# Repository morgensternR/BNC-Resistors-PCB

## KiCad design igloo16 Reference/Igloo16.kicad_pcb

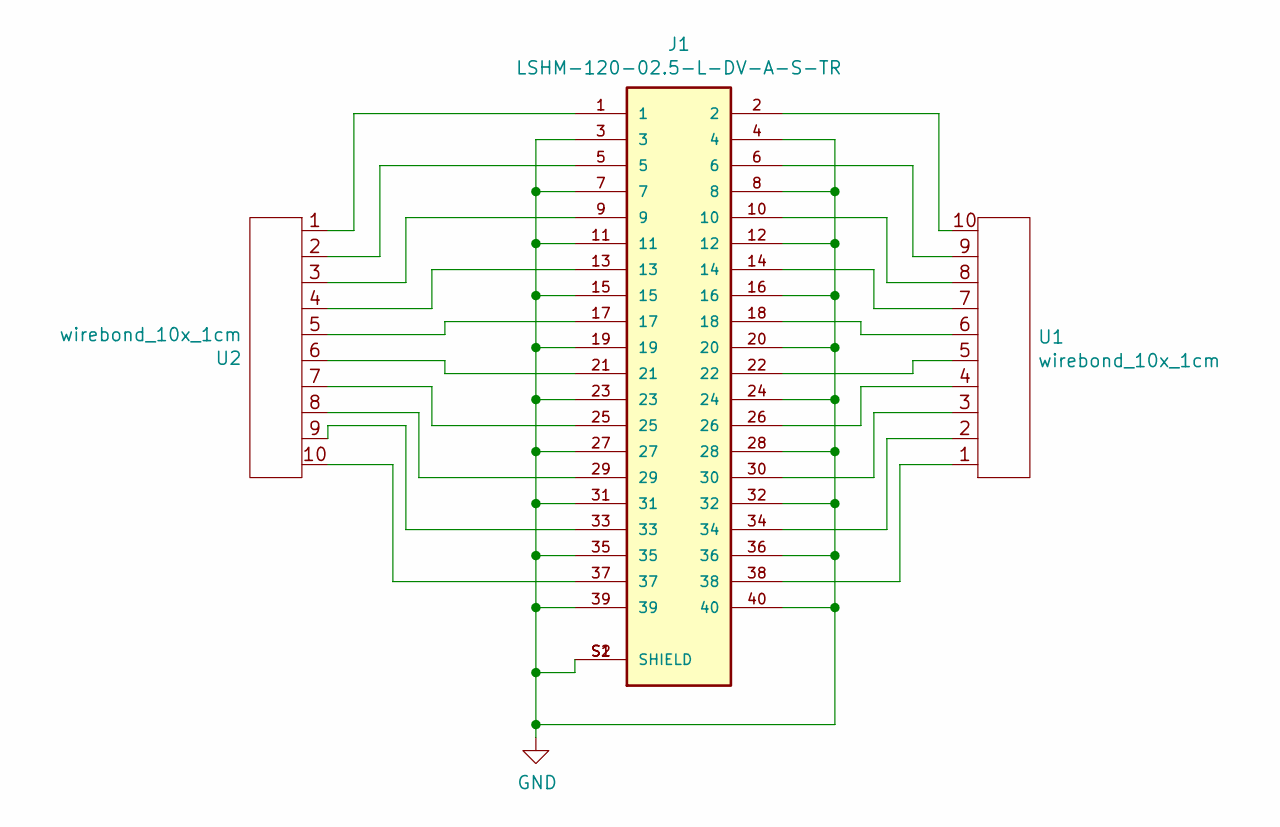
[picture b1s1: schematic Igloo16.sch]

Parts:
J1: LSHM-120-02.5-L-DV-A-S-TR; SAMTEC_LSHM-120-02.5-L-DV-A-S-TR
U1, U2: wirebond_10x_1cm

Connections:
GND: J1.3, J1.4, J1.7, J1.8, J1.11, J1.12, J1.15, J1.16, J1.19, J1.20, J1.23, J1.24, J1.27, J1.28, J1.31, J1.32, J1.35, J1.36, J1.39, J1.40, J1.S1 (SHIELD), J1.S2 (SHIELD)
unnamed: J1.1, U2.1
unnamed: J1.2, U1.10
unnamed: J1.5, U2.2
unnamed: J1.6, U1.9
unnamed: J1.9, U2.3
unnamed: J1.10, U1.8
unnamed: J1.13, U2.4
unnamed: J1.14, U1.7
unnamed: J1.17, U2.5
unnamed: J1.18, U1.6
unnamed: J1.21, U2.6
unnamed: J1.22, U1.5
unnamed: J1.25, U2.7
unnamed: J1.26, U1.4
unnamed: J1.29, U2.8
unnamed: J1.30, U1.3
unnamed: J1.33, U2.9
unnamed: J1.34, U1.2
unnamed: J1.37, U2.10
unnamed: J1.38, U1.1

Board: 2 copper layers, 3 parts (1 on the bottom side), 21 nets, no tracks yet.

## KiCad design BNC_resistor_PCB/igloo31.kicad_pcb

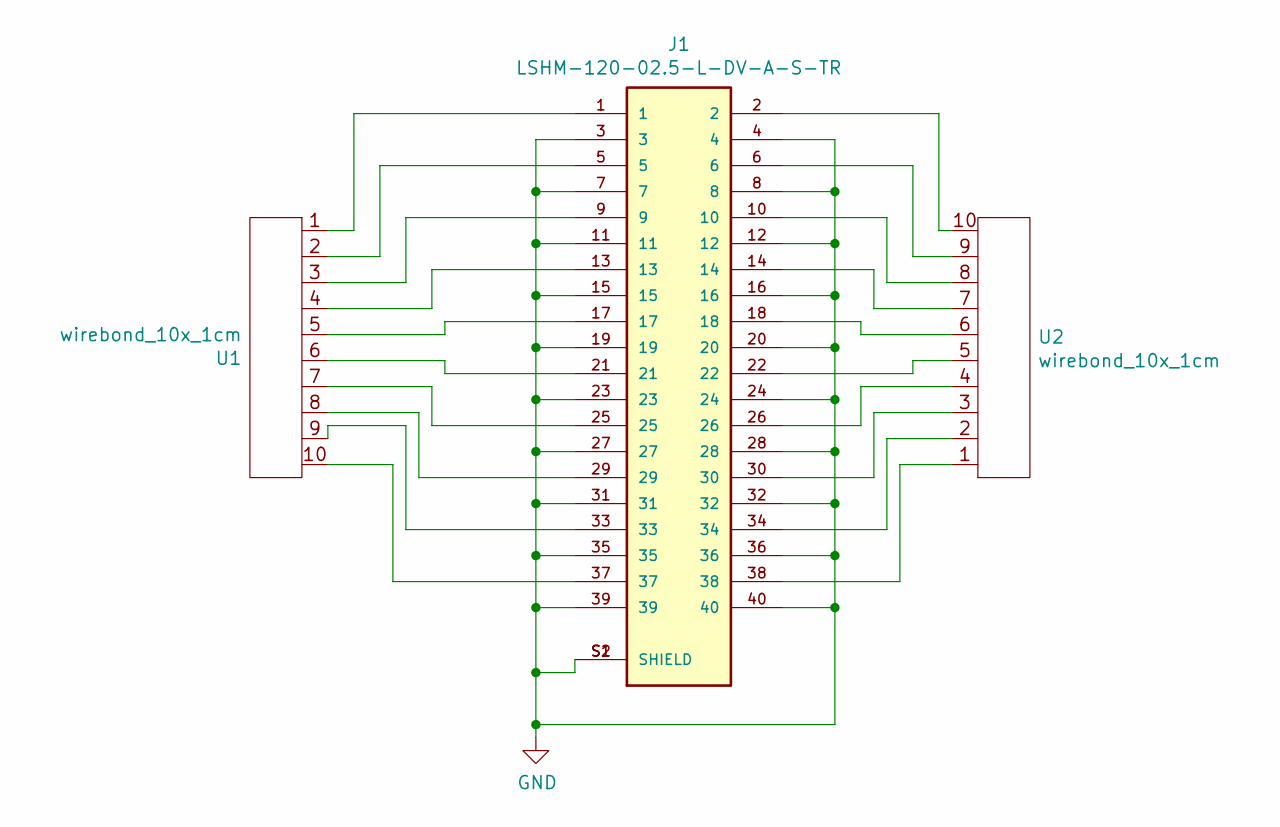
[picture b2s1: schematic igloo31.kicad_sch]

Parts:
J1: LSHM-120-02.5-L-DV-A-S-TR; SAMTEC_LSHM-120-02.5-L-DV-A-S-TR
U1, U2: wirebond_10x_1cm

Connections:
GND: J1.3, J1.4, J1.7, J1.8, J1.11, J1.12, J1.15, J1.16, J1.19, J1.20, J1.23, J1.24, J1.27, J1.28, J1.31, J1.32, J1.35, J1.36, J1.39, J1.40, J1.S1 (SHIELD), J1.S2 (SHIELD)
unnamed: J1.1, U1.1
unnamed: J1.2, U2.10
unnamed: J1.5, U1.2
unnamed: J1.6, U2.9
unnamed: J1.9, U1.3
unnamed: J1.10, U2.8
unnamed: J1.13, U1.4
unnamed: J1.14, U2.7
unnamed: J1.17, U1.5
unnamed: J1.18, U2.6
unnamed: J1.21, U1.6
unnamed: J1.22, U2.5
unnamed: J1.25, U1.7
unnamed: J1.26, U2.4
unnamed: J1.29, U1.8
unnamed: J1.30, U2.3
unnamed: J1.33, U1.9
unnamed: J1.34, U2.2
unnamed: J1.37, U1.10
unnamed: J1.38, U2.1

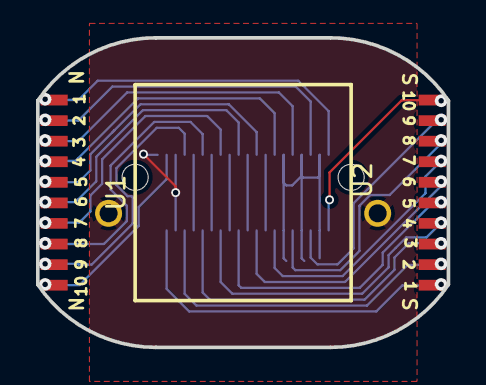
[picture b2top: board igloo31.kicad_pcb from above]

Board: 2 copper layers, 22.8 x 17.2 mm, 3 parts (1 on the bottom side), 21 nets.

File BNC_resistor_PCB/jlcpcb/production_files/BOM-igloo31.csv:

Comment,Designator,Footprint,LCSC
LSHM-120-02.5-L-DV-A-S-TR,J1,SAMTEC_LSHM-120-02.5-L-DV-A-S-TR,
wirebond_10x_1cm,U2,wirebond_10x_1cm,
wirebond_10x_1cm,U1,wirebond_10x_1cm,

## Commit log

2024-03-01 changed file names
